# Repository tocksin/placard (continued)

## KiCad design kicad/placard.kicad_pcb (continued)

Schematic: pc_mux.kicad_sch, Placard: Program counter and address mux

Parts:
C3, C4, C7, C8, C9, C10: 100n; C_Disc_D5.0mm_W2.5mm_P5.00mm; MPN FG28X7R1H104KNT00
U3, U4, U7, U8, U9, U10: ATF22V10C-7PX; DIP-24_W7.62mm_Socket_Puller; MPN ATF22V10C-7PX

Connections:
+5V: C3.1, C4.1, C7.1, C8.1, C9.1, C10.1, U3.13 (CIN), U3.24 (VCC), U4.24 (VCC), U7.24 (VCC), U8.24 (VCC), U9.24 (VCC), U10.24 (VCC); also elsewhere on the board
ADDR0: U7.20 (LO0); also elsewhere on the board
ADDR1: U7.21 (LO1); also elsewhere on the board
ADDR2: U8.20 (LO0); also elsewhere on the board
ADDR3: U8.21 (LO1); also elsewhere on the board
ADDR4: U9.20 (LO0); also elsewhere on the board
ADDR5: U9.21 (LO1); also elsewhere on the board
ADDR6: U10.20 (LO0); also elsewhere on the board
ADDR7: U10.21 (LO1); also elsewhere on the board
ADDR8: U7.22 (HI0); also elsewhere on the board
ADDR9: U7.23 (HI1); also elsewhere on the board
ADDR10: U8.22 (HI0); also elsewhere on the board
ADDR11: U8.23 (HI1); also elsewhere on the board
ADDR12: U9.22 (HI0); also elsewhere on the board
ADDR13: U9.23 (HI1); also elsewhere on the board
ADDR14: U10.22 (HI0); also elsewhere on the board
ADDR15: U10.23 (HI1); also elsewhere on the board
CLK: U3.1 (CLK), U4.1 (CLK); also elsewhere on the board
D0: U7.5 (D0); also elsewhere on the board
D1: U7.9 (D1); also elsewhere on the board
D2: U8.5 (D0); also elsewhere on the board
D3: U8.9 (D1); also elsewhere on the board
D4: U9.5 (D0); also elsewhere on the board
D5: U9.9 (D1); also elsewhere on the board
D6: U10.5 (D0); also elsewhere on the board
D7: U10.9 (D1); also elsewhere on the board
DATABUS0: U3.2 (D0); also elsewhere on the board
DATABUS1: U3.3 (D1); also elsewhere on the board
DATABUS2: U3.4 (D2); also elsewhere on the board
DATABUS3: U3.5 (D3); also elsewhere on the board
DATABUS4: U3.6 (D4); also elsewhere on the board
DATABUS5: U3.7 (D5); also elsewhere on the board
DATABUS6: U3.8 (D6); also elsewhere on the board
DATABUS7: U3.9 (D7); also elsewhere on the board
GND: C3.2, C4.2, C7.2, C8.2, C9.2, C10.2, U3.12 (GND), U4.12 (GND), U7.12 (GND), U8.12 (GND), U9.12 (GND), U10.12 (GND); also elsewhere on the board
H3: U7.18 (V3); also elsewhere on the board
H4: U8.15 (V2); also elsewhere on the board
H5: U8.18 (V3); also elsewhere on the board
H6: U9.15 (V2); also elsewhere on the board
H7: U9.18 (V3); also elsewhere on the board
H8: U10.15 (V2); also elsewhere on the board
H9: U10.18 (V3); also elsewhere on the board
LOAD_PC_HIGH: U4.10 (LOAD); also elsewhere on the board
LOAD_PC_LOW: U3.10 (LOAD); also elsewhere on the board
unnamed: U3.23 (CO), U4.13 (CIN)
PC0: U3.15 (Q0), U7.8 (PC0)
PC1: U3.22 (Q1), U7.13 (PC1)
PC2: U3.21 (Q2), U8.8 (PC0)
PC3: U3.16 (Q3), U8.13 (PC1)
PC4: U3.20 (Q4), U9.8 (PC0)
PC5: U3.17 (Q5), U9.13 (PC1)
PC6: U3.19 (Q6), U10.8 (PC0)
PC7: U3.18 (Q7), U10.13 (PC1)
PC8: U4.15 (Q0), U7.16 (PC2)
PC9: U4.22 (Q1), U7.19 (PC3)
PC10: U4.21 (Q2), U8.16 (PC2)
PC11: U4.16 (Q3), U8.19 (PC3)
PC12: U4.20 (Q4), U9.16 (PC2)
PC13: U4.17 (Q5), U9.19 (PC3)
PC14: U4.19 (Q6), U10.16 (PC2)
PC15: U4.18 (Q7), U10.19 (PC3); also elsewhere on the board
PC_ENABLE: U3.11 (EN), U4.11 (EN), U7.2 (PC_ENABLE), U8.2 (PC_ENABLE), U9.2 (PC_ENABLE), U10.2 (PC_ENABLE); also elsewhere on the board
PIXEL_ENABLE: U7.1 (PIXEL_ENABLE), U8.1 (PIXEL_ENABLE), U9.1 (PIXEL_ENABLE), U10.1 (PIXEL_ENABLE); also elsewhere on the board
STALL_OUT: U3.14 (PIXEL_ENABLE), U4.14 (PIXEL_ENABLE); also elsewhere on the board
V2: U8.7 (V0); also elsewhere on the board
V3: U8.11 (V1); also elsewhere on the board
V4: U9.7 (V0); also elsewhere on the board
V5: U9.11 (V1); also elsewhere on the board
V6: U10.7 (V0); also elsewhere on the board
VA0: U7.7 (V0); also elsewhere on the board
VA1: U7.11 (V1); also elsewhere on the board
VA7: U10.11 (V1); also elsewhere on the board
VA8: U7.15 (V2); also elsewhere on the board
X0: U7.6 (X0); also elsewhere on the board
X1: U7.10 (X1); also elsewhere on the board
X2: U8.6 (X0); also elsewhere on the board
X3: U8.10 (X1); also elsewhere on the board
X4: U9.6 (X0); also elsewhere on the board
X5: U9.10 (X1); also elsewhere on the board
X6: U10.6 (X0); also elsewhere on the board
X7: U10.10 (X1); also elsewhere on the board
X_ENABLE: U7.3 (X_ENABLE), U8.3 (X_ENABLE), U9.3 (X_ENABLE), U10.3 (X_ENABLE); also elsewhere on the board
Y0: U4.2 (D0), U7.14 (Y2); also elsewhere on the board
Y1: U4.3 (D1), U7.17 (Y3); also elsewhere on the board
Y2: U4.4 (D2), U8.14 (Y2); also elsewhere on the board
Y3: U4.5 (D3), U8.17 (Y3); also elsewhere on the board
Y4: U4.6 (D4), U9.14 (Y2); also elsewhere on the board
Y5: U4.7 (D5), U9.17 (Y3); also elsewhere on the board
Y6: U4.8 (D6), U10.14 (Y2); also elsewhere on the board
Y7: U4.9 (D7), U10.17 (Y3); also elsewhere on the board
Y_ENABLE: U7.4 (Y_ENABLE), U8.4 (Y_ENABLE), U9.4 (Y_ENABLE), U10.4 (Y_ENABLE); also elsewhere on the board

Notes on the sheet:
Each mux: two low bits (D, X, video, PC) and two high bits (0, Y, video, PC); the enables select
Selects: PIXEL_ENABLE (U15) = video address; else PC_ENABLE = PC; else X_ENABLE / Y_ENABLE = X / Y register; else D / 00h.
Video address: VA0, VA1, VA7, VA8 from the audio slot PLD (line repeat), ADDR6:2 = V6:V2, ADDR15:9 = H9:H3.
Program counter and address mux
U3 CIN tied high (always counts); U3 CO carries into U4. STALL_OUT holds the PC (video reads, ALU wait, cartridge load).

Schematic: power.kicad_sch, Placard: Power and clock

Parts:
C40, C47: 1u; C_Disc_D5.0mm_W2.5mm_P5.00mm; MPN C330C105K5R5TA
C41: 220u; CP_Radial_D6.3mm_P2.50mm; MPN 25YXJ220M6.3X11
C43: 100n; C_Disc_D5.0mm_W2.5mm_P5.00mm; MPN FG28X7R1H104KNT00
D7: SA5.0A; D_DO-15_P10.16mm_Horizontal; MPN SA5.0A
D8: 1N5817; D_DO-41_SOD81_P7.62mm_Horizontal_Pad1.6; MPN 1N5817-TP
D18: WP7113ID; LED_D5.0mm; MPN WP7113ID
F1: 3 A hold; Fuse_Bourns_MF-RG300; MPN MF-RG300-0
J13: USB4125-GF-A; USB_C_Receptacle_GCT_USB4125_6P_HandSolder; MPN USB4125-GF-A-0190
JP1: STALL; PinHeader_1x02_P2.54mm_Vertical; MPN PREC002SAAN-RC
JP2: RUN; PinHeader_1x02_P2.54mm_Vertical; MPN PREC002SAAN-RC
K1: J1071CS5VDC.36; Relay_SPDT_CIT_J107; MPN J1071CS5VDC.36
NT1: AGND tie; NetTie-2_THT_Pad0.3mm
NT2: CLK tap; NetTie-2_THT_Pad0.3mm
R1, R2: 5.1k; R_Axial_DIN0207_L6.3mm_D2.5mm_P10.16mm_Horizontal_Value; MPN MFR-25FBF52-5K1
R3, R4: 10k; R_Axial_DIN0207_L6.3mm_D2.5mm_P10.16mm_Horizontal_Value; MPN MFR-25FBF52-10K
R59: 1k; R_Axial_DIN0207_L6.3mm_D2.5mm_P10.16mm_Horizontal_Value; MPN MFR-25FBF52-1K
R64: 22; R_Axial_DIN0207_L6.3mm_D2.5mm_P10.16mm_Horizontal_Value; MPN MFR-25FBF52-22R
SW1: ANT11TFHQE; SW_Toggle_CIT_ANT11TFHQE; MPN ANT11TFHQE
SW2: PTS645VL58-2 LFS; SW_Tactile_SPST_Angled_PTS645Vx58-2LFS; MPN PTS645VL58-2 LFS
TP1, TP2: GND; TestPoint_Keystone_5010-5014_Multipurpose; MPN 5011
TP3: +5V; TestPoint_Keystone_5010-5014_Multipurpose; MPN 5010
U40: MCP1700-3302E/TO; TO-92_Inline; MPN MCP1700-3302E/TO
X1: 25.175 MHz; Oscillator_DIP-14; MPN ECS-100A-251.7

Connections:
+3V3: C47.1, U40.3 (VO); also elsewhere on the board
+5V: C40.1, C41.1, C43.1, JP2.2 (B), K1.1, R3.1, R59.1, TP3.1, U40.2 (VI), X1.14 (VCC); also elsewhere on the board
/Power and clock/VON: K1.4, SW1.2 (B), SW2.1
CLK: NT2.2; also elsewhere on the board
CLK_E: NT2.1, X1.8 (OUT); also elsewhere on the board
GND: C40.2, C41.2, C43.2, C47.2, D7.2 (A), D8.2 (A), D18.1 (K), J13.A12 (GND), J13.B12 (GND), J13.S1 (SHIELD), K1.2, NT1.1, R1.2, R2.2, R4.2, R64.2, TP1.1, TP2.1, U40.1 (GND), X1.7 (GND); also elsewhere on the board
GNDA: NT1.2; also elsewhere on the board
unnamed: D7.1 (K), F1.2, SW1.1 (A)
unnamed: D8.1 (K), K1.5, SW2.2
unnamed: D18.2 (A), R59.2
unnamed: F1.1, J13.A9 (VBUS), J13.B9 (VBUS)
unnamed: J13.A5 (CC1), R1.1
unnamed: J13.B5 (CC2), R2.1
unnamed: K1.3, R64.1
RUN: JP2.1 (A), R4.1; also elsewhere on the board
STALL_IN: JP1.1 (A); also elsewhere on the board
STALL_OUT: JP1.2 (B), R3.2; also elsewhere on the board

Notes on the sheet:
here, at the power input
19 PLDs draw up to about 2.5 A (130 mA each at
-7, worst case): use a 3 A supply; the polyfuse
cartridge: STALL_IN (the Branch PLD's STALL) goes out to it.
5.1k on CC1 and CC2: a USB-C source gives 5 V.
AGND (audio) meets GND
USB-C 5 V in, 3.3 V for the SD card, 25.175 MHz oscillator (CLK), cartridge STALL and RUN
NT2: CLK_E (X1, U15 pin 9, U11 pin 1) to CLK (every other chip) through
D18 power LED (red, 5 mm) on +5V,
STALL_OUT (10k up) and RUN (10k down) come from the
one throw. SW2 reset: holding it pulls in K1,
TP1, TP2 GND (black Keystone 5011), TP3 +5V after K1
Power and clock
C40 input, C47 output (1 uF ceramic).
+5V via R64. C41 rides out the release bounce.
Without one, fit JP1 and JP2 for bring-up
R59 1k: about 3 mA.
whose NC contact opens the 5 V line; NO drains
after K1: dark while reset is held.
U40: 3.3 V for the SD card only (sheet 10).
(red 5010): clip points for the bring-up test leads.
at least 420 mm of track (500 nominal): the RAM /WE's early clock.
trips on a short. SW1 power: toggle, common +
(BRINGUP.md); take them out with a cartridge.

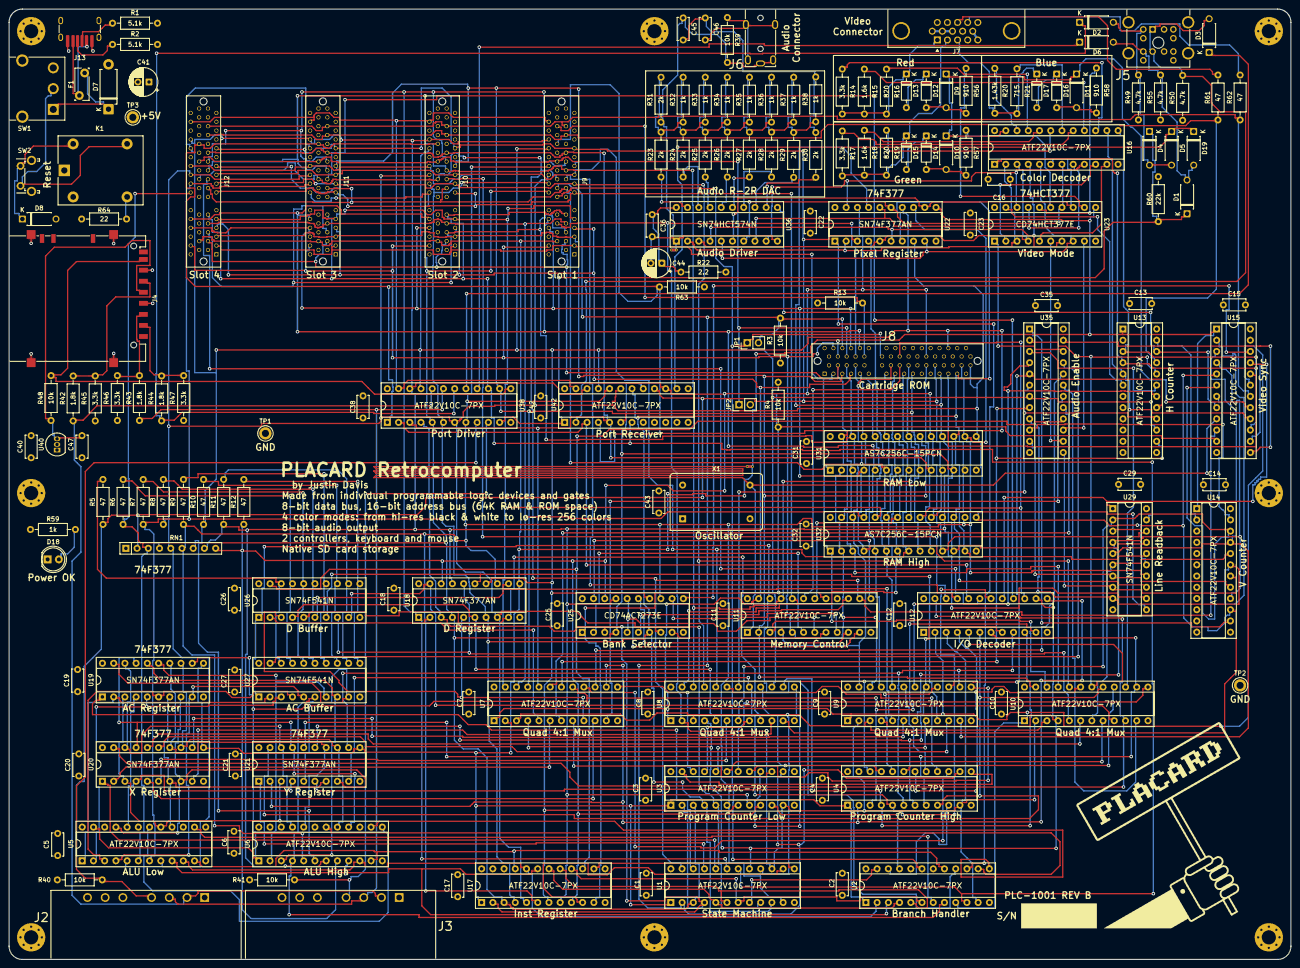
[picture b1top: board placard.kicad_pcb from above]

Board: 4 copper layers, 290.0 x 215.0 mm, 187 parts (0 on the bottom side), 255 nets.

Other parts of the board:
H1, H2, H3, H4, H5, H6, H7, H8: M3; MountingHole_3.2mm_M3_Pad_Via
LOGO1: PLACARD_Logo

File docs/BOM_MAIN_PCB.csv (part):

Qty,References,Part number,Manufacturer,Description,Value,Unit price USD,Line total USD,Price from,Notes,Footprint,On schematic
1,,PLC-1001 rev A,(custom PCB),"PCB, main board, 290 x 215 mm, 4-layer, 1.6 mm, HASL lead-free",,16.00,16.00,"est.: JLCPCB/PCBWay typical, KIT_PRICING.md",,,no
20,U1 U2 U3 U4 U5 U6 U7 U8 U9 U10 U11 U12 U13 U14 U15 U16 U17 U35 U38 U42,ATF22V10C-7PX,Microchip,"PLD, 22V10, 7.5 ns, PDIP-24 0.3"" (programmed)",,2.99,59.80,Mouser,"State U1; Branch U2; PC U3, U4; ALU U5, U6; Address mux U7-U10; Memory control U11; I/O decode U12; H counter U13; V counter U14; Sync U15; Color decoder U16; Instruction register U17; Audio slot U35; Shared port U38; PS/2 receiver U42",placard:DIP-24_W7.62mm_Socket_Puller,yes
5,U18 U19 U20 U21 U22,SN74F377AN,Texas Instruments,"Octal D flip-flop with enable, 74F, DIP-20",,1.54,7.70,Mouser,,placard:DIP-20_W7.62mm_Socket_Puller,yes
1,U23,CD74HCT377E,Texas Instruments,"Octal D flip-flop with enable, 74HCT, DIP-20 (line code: drives the row tint)",,1.29,1.29,Mouser,,placard:DIP-20_W7.62mm_Socket_Puller,yes
1,U25,CD74ACT273E,Texas Instruments,"Octal D flip-flop with clear, 74ACT, DIP-20",,2.45,2.45,Mouser,,placard:DIP-20_W7.62mm_Socket_Puller,yes
3,U26 U27 U29,SN74F541N,Texas Instruments,"Octal buffer, 3-state, 74F, DIP-20",,1.49,4.47,Mouser,,placard:DIP-20_W7.62mm_Socket_Puller,yes
2,U31 U32,AS7C256C-15PCN,Alliance Memory,"SRAM, 32K x 8, 15 ns, PDIP-28 0.3""",,15.21,30.42,Mouser,,placard:DIP-28_W7.62mm_Socket_Puller,yes
1,U36,SN74HCT574N,Texas Instruments,"Octal D flip-flop, 3-state, 74HCT, DIP-20",,1.46,1.46,Mouser,,placard:DIP-20_W7.62mm_Socket_Puller,yes
1,U40,MCP1700-3302E/TO,Microchip,"3.3 V LDO regulator, 250 mA, TO-92",,0.50,0.50,Mouser,,placard:TO-92_Inline,yes
1,X1,ECS-100A-251.7,ECS Inc.,"Clock oscillator, 25.175 MHz, 5 V, full-size DIP-14 can",25.175 MHz,4.06,4.06,"Digi-Key: Mouser has no stock (Justin, 2026-10-22)",,placard:Oscillator_DIP-14,yes
2,J2 J3,,,"SNES controller socket, 7 pin",SNES pad,4.00,8.00,est.: ZedLabz right-angle SNES port (Amazon/eBay),,placard:SNES_Pad_Socket_Horizontal,yes
1,J4,DM1AA-SF-PEJ(82),Hirose,SD card socket,SD (SPI),4.56,4.56,"Mouser: SMD, push-push (no horizontal through-hole SD socket exists; Kyocera 145638009511859+ went obsolete 2026-10-25)",,placard:SD_Hirose_DM1AA_SF_PEJ82,yes
1,J5,KMDGX-6S/6S-S4N,Kycon,"Stacked dual mini-DIN-6 receptacle (PS/2), right angle, shielded: mouse top, keyboard bottom",PS/2 kbd + mouse,3.72,3.72,Mouser,,placard:PS2_Kycon_KMDGX-6S-6S-S4N,yes
1,J6,54-00174,Tensility,"3.5 mm audio line out jack, 4 pole (TRRS), right angle, TH (a TRS plug's sleeve spans R2 and S)",3.5 mm,0.73,0.73,"Digi-Key: Justin, 2026-10-22",,placard:Jack_3.5mm_Tensility_54-00174_Horizontal,yes
1,J7,A-HDF 15 A-KG/T,Assmann WSW,"DE-15 high-density receptacle (VGA), with mounting holes",VGA,1.36,1.36,"Digi-Key: Justin, 2026-10-22",,placard:DSUB-15-HD_Female_Horizontal_P2.29x1.98mm_EdgePinOffset3.03mm_Housed_MountingHolesOffset4.94mm,yes
1,J8,87715-9106,Molex,"Cartridge slot: card edge, 64 contacts, 1.0 mm, keyed (PCIe x4 style), vertical TH",,2.88,2.88,Mouser,,placard:Molex_87715-9106_PCIe_x4_Vertical,yes
4,J9 J10 J11 J12,87715-9106,Molex,"Expansion slot: card edge, 64 contacts, 1.0 mm, keyed (PCIe x4 style), vertical TH, as the cartridge slot",,2.88,11.52,Mouser,"Optional (Justin, 2026-10-22): fit only the slots a card will go in; the computer runs with none.  The cartridge slot's connector since 2026-10-30 (EXPANSION.md)",placard:Molex_87715-9106_Expansion_Slot,yes
1,J13,USB4125-GF-A-0190,GCT,"USB-C receptacle, power only (6 pin), top mount",USB4125-GF-A,0.61,0.61,Mouser,,placard:USB_C_Receptacle_GCT_USB4125_6P_HandSolder,yes
1,SW1,ANT11TFHQE,CIT Relay and Switch,"Power on/off: SPDT on-on toggle, 5 A 28 V DC, right-angle PCB, 1/4-40 bushing",,4.50,4.50,est.: Digi-Key; Mouser has no stock,,placard:SW_Toggle_CIT_ANT11TFHQE,yes
1,SW2,PTS645VL58-2 LFS,C&K,"Reset button: tactile, SPST momentary, right angle, through hole (drives K1's coil)",,0.43,0.43,est.: Digi-Key; Mouser has no stock until 12/23/2026,,placard:SW_Tactile_SPST_Angled_PTS645Vx58-2LFS,yes
1,K1,J1071CS5VDC.36,CIT Relay and Switch,"Reset relay: SPDT, 5 V coil (69 ohm, 72 mA), 7 A 30 V DC (NO and NC), through hole, sealed; NC contact carries the 5 V",,1.15,1.15,"Digi-Key: Justin, 2026-10-25; Mouser does not sell CIT",,placard:Relay_SPDT_CIT_J107,yes
1,F1,MF-RG300-0,Bourns,"Polyfuse, 3 A hold, radial",3 A hold,0.73,0.73,Mouser,Part number from the footprint (Fuse_Bourns_MF-RG300),placard:Fuse_Bourns_MF-RG300,yes
11,D1 D2 D3 D4 D5 D6 D8 D9 D10 D11 D19,1N5817-TP,Micro Commercial Co,"Schottky diode, 1 A, DO-41 (black)",1N5817,0.15,1.65,est.: MCC 1N5817-TP,"Black DO-41 Schottky, so it is not mixed up with the glass 1N4148s; any 1N5817 (MCC, onsemi, Diodes Inc.)",placard:D_DO-41_SOD81_P7.62mm_Horizontal_Pad1.6,yes
1,D7,SA5.0A,Littelfuse,"TVS diode, 5 V stand-off, 500 W, DO-15 axial (across the fused USB 5 V)",,0.64,0.64,Mouser,,placard:D_DO-15_P10.16mm_Horizontal,yes
6,D12 D13 D14 D15 D16 D17,1N4148-TAP,Vishay,"Small-signal diode, DO-35 (glass)",1N4148,0.26,1.56,Mouser: Vishay 1N4148-TAP,"Any 1N4148 (Vishay, onsemi, Diodes Inc.)",placard:D_DO-35_SOD27_P7.62mm_Horizontal,yes
1,D18,WP7113ID,Kingbright,"Power LED, 5 mm, red diffused, through hole (on +5V after K1)",,0.21,0.21,Mouser,"D18 with R59 (1k, about 3 mA); any 5 mm LED fits, pick the color (was Lite-On LTL2R3KRD-EM, out of stock 2026-10-25)",placard:LED_D5.0mm,yes
2,R1 R2,MFR-25FBF52-5K1,Yageo,"Resistor, metal film 1%, 1/4 W, axial",5.1k,0.10,0.20,est.: Yageo MFR-25FBF52 series,,placard:R_Axial_DIN0207_L6.3mm_D2.5mm_P10.16mm_Horizontal_Value,yes
8,R3 R4 R13 R39 R40 R41 R48 R63,MFR-25FBF52-10K,Yageo,"Resistor, metal film 1%, 1/4 W, axial",10k,0.10,0.80,est.: Yageo MFR-25FBF52 series,,placard:R_Axial_DIN0207_L6.3mm_D2.5mm_P10.16mm_Horizontal_Value,yes
10,R5 R6 R7 R8 R9 R10 R11 R12 R61 R62,MFR-25FBF52-47R,Yageo,"Resistor, metal film 1%, 1/4 W, axial",47,0.04,0.40,est.: Yageo MFR-25FBF52 series,,placard:R_Axial_DIN0207_L6.3mm_D2.5mm_P10.16mm_Horizontal_Value,yes
5,R14 R17 R45 R46 R47,MFR-25FBF52-3K3,Yageo,"Resistor, metal film 1%, 1/4 W, axial",3.3k,0.10,0.50,est.: Yageo MFR-25FBF52 series,,placard:R_Axial_DIN0207_L6.3mm_D2.5mm_P10.16mm_Horizontal_Value,yes
2,R15 R18,MFR-25FBF52-1K6,Yageo,"Resistor, metal film 1%, 1/4 W, axial",1.6k,0.10,0.20,est.: Yageo MFR-25FBF52 series,,placard:R_Axial_DIN0207_L6.3mm_D2.5mm_P10.16mm_Horizontal_Value,yes
2,R16 R19,MFR-25FBF52-820R,Yageo,"Resistor, metal film 1%, 1/4 W, axial",820,0.10,0.20,est.: Yageo MFR-25FBF52 series,,placard:R_Axial_DIN0207_L6.3mm_D2.5mm_P10.16mm_Horizontal_Value,yes
1,R20,MFR-25FBF52-1K43,Yageo,"Resistor, metal film 1%, 1/4 W, axial",1.43k,0.10,0.10,est.: Yageo MFR-25FBF52 series,,placard:R_Axial_DIN0207_L6.3mm_D2.5mm_P10.16mm_Horizontal_Value,yes
1,R21,MFR-25FBF52-715R,Yageo,"Resistor, metal film 1%, 1/4 W, axial",715,0.10,0.10,est.: Yageo MFR-25FBF52 series,,placard:R_Axial_DIN0207_L6.3mm_D2.5mm_P10.16mm_Horizontal_Value,yes
1,R22,MFR-25FBF52-2R2,Yageo,"Resistor, metal film 1%, 1/4 W, axial",2.2,0.10,0.10,est.: Yageo MFR-25FBF52 series,,placard:R_Axial_DIN0207_L6.3mm_D2.5mm_P10.16mm_Horizontal_Value,yes
9,R23 R24 R25 R26 R27 R28 R29 R30 R31,MFR-25FBF52-2K,Yageo,"Resistor, metal film 1%, 1/4 W, axial",2k,0.10,0.90,est.: Yageo MFR-25FBF52 series,,placard:R_Axial_DIN0207_L6.3mm_D2.5mm_P10.16mm_Horizontal_Value,yes
12,R32 R33 R34 R35 R36 R37 R38 R51 R52 R53 R54 R59,MFR-25FBF52-1K,Yageo,"Resistor, metal film 1%, 1/4 W, axial",1k,0.04,0.48,est.: Yageo MFR-25FBF52 series,,placard:R_Axial_DIN0207_L6.3mm_D2.5mm_P10.16mm_Horizontal_Value,yes
3,R42 R43 R44,MFR-25FBF52-1K8,Yageo,"Resistor, metal film 1%, 1/4 W, axial",1.8k,0.10,0.30,est.: Yageo MFR-25FBF52 series,,placard:R_Axial_DIN0207_L6.3mm_D2.5mm_P10.16mm_Horizontal_Value,yes
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
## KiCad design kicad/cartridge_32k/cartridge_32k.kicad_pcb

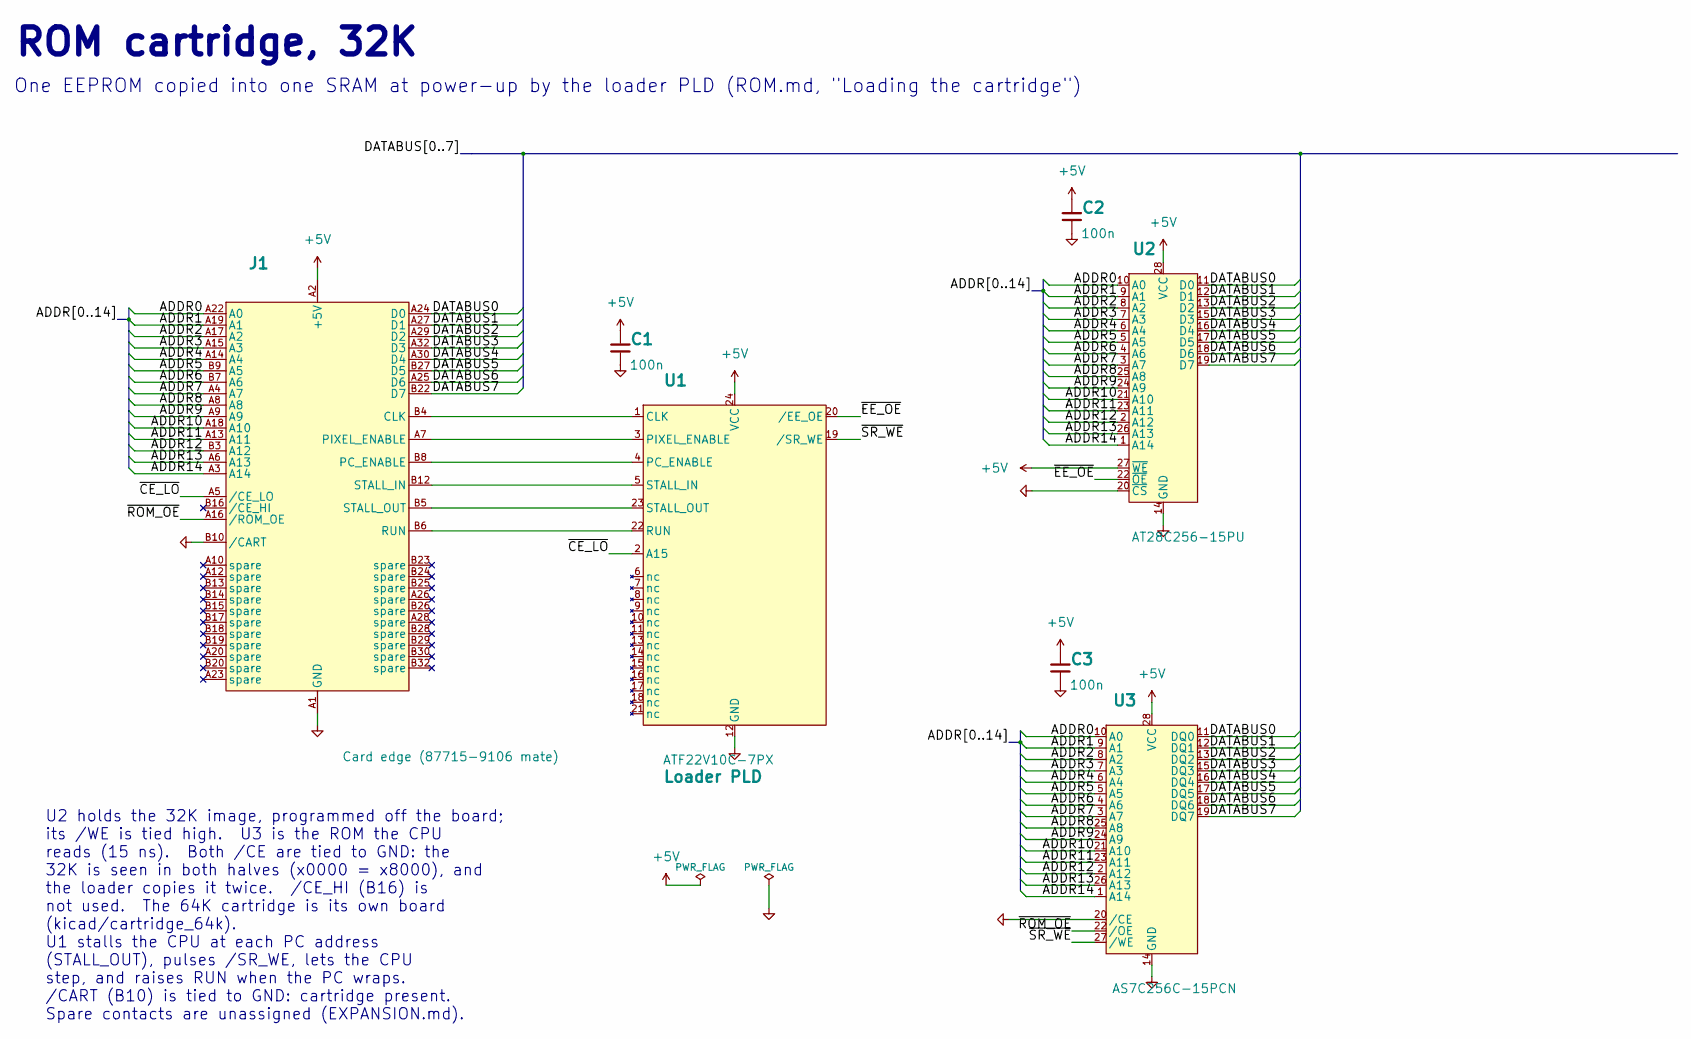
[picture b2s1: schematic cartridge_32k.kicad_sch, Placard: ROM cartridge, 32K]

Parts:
C1, C2, C3: 100n; C_Disc_D5.0mm_W2.5mm_P5.00mm; MPN FG28X7R1H104KNT00
J1: Card edge (87715-9106 mate); Card_Edge_87715-9106
U1: ATF22V10C-7PX; DIP-24_W7.62mm_Socket_Puller; MPN ATF22V10C-7PX
U2: AT28C256-15PU; DIP-28_W15.24mm_Socket_Puller; MPN AT28C256-15PU
U3: AS7C256C-15PCN; DIP-28_W7.62mm_Socket_Puller; MPN AS7C256C-15PCN

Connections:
+5V: C1.1, C2.1, C3.1, J1.A2 (+5V), J1.B2 (+5V), U1.24 (VCC), U2.27 (~WE), U2.28 (VCC), U3.28 (VCC)
/ADDR0: J1.A22 (A0), U2.10 (A0), U3.10 (A0)
/ADDR1: J1.A19 (A1), U2.9 (A1), U3.9 (A1)
/ADDR2: J1.A17 (A2), U2.8 (A2), U3.8 (A2)
/ADDR3: J1.A15 (A3), U2.7 (A3), U3.7 (A3)
/ADDR4: J1.A14 (A4), U2.6 (A4), U3.6 (A4)
/ADDR5: J1.B9 (A5), U2.5 (A5), U3.5 (A5)
/ADDR6: J1.B7 (A6), U2.4 (A6), U3.4 (A6)
/ADDR7: J1.A4 (A7), U2.3 (A7), U3.3 (A7)
/ADDR8: J1.A8, U2.25 (A8), U3.25 (A8)
/ADDR9: J1.A9, U2.24 (A9), U3.24 (A9)
/ADDR10: J1.A18 (A10), U2.21 (A10), U3.21 (A10)
/ADDR11: J1.A13 (A11), U2.23 (A11), U3.23 (A11)
/ADDR12: J1.B3 (A12), U2.2 (A12), U3.2 (A12)
/ADDR13: J1.A6 (A13), U2.26 (A13), U3.26 (A13)
/ADDR14: J1.A3 (A14), U2.1 (A14), U3.1 (A14)
/DATABUS0: J1.A24 (D0), U2.11 (D0), U3.11 (DQ0)
/DATABUS1: J1.A27 (D1), U2.12 (D1), U3.12 (DQ1)
/DATABUS2: J1.A29 (D2), U2.13 (D2), U3.13 (DQ2)
/DATABUS3: J1.A32 (D3), U2.15 (D3), U3.15 (DQ3)
/DATABUS4: J1.A30 (D4), U2.16 (D4), U3.16 (DQ4)
/DATABUS5: J1.B27 (D5), U2.17 (D5), U3.17 (DQ5)
/DATABUS6: J1.A25 (D6), U2.18 (D6), U3.18 (DQ6)
/DATABUS7: J1.B22 (D7), U2.19 (D7), U3.19 (DQ7)
/~CE_LO: J1.A5 (/CE_LO), U1.2 (A15)
/~EE_OE: U1.20 (/EE_OE), U2.22 (~OE)
/~ROM_OE: J1.A16 (/ROM_OE), U3.22 (/OE)
/~SR_WE: U1.19 (/SR_WE), U3.27 (/WE)
GND: C1.2, C2.2, C3.2, J1.A1 (GND), J1.A11 (GND), J1.A21 (GND), J1.A31 (GND), J1.B1 (GND), J1.B10 (/CART), J1.B11 (GND), J1.B21 (GND), J1.B31 (GND), U1.12 (GND), U2.14 (GND), U2.20 (~CS), U3.14 (GND), U3.20 (/CE)
unnamed: J1.B4 (CLK), U1.1 (CLK)
unnamed: J1.B8 (PC_ENABLE), U1.4 (PC_ENABLE)
unnamed: J1.A7 (PIXEL_ENABLE), U1.3 (PIXEL_ENABLE)
unnamed: J1.B6 (RUN), U1.22 (RUN)
unnamed: J1.B12 (STALL_IN), U1.5 (STALL_IN)
unnamed: J1.B5 (STALL_OUT), U1.23 (STALL_OUT)

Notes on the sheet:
ROM cartridge, 32K
One EEPROM copied into one SRAM at power-up by the loader PLD (ROM.md, "Loading the cartridge")
U2 holds the 32K image, programmed off the board;
its /WE is tied high. U3 is the ROM the CPU
reads (15 ns). Both /CE are tied to GND: the
32K is seen in both halves (x0000 = x8000), and
the loader copies it twice. /CE_HI (B16) is
not used. The 64K cartridge is its own board
(kicad/cartridge_64k).
U1 stalls the CPU at each PC address
(STALL_OUT), pulses /SR_WE, lets the CPU
step, and raises RUN when the PC wraps.
/CART (B10) is tied to GND: cartridge present.
Spare contacts are unassigned (EXPANSION.md).

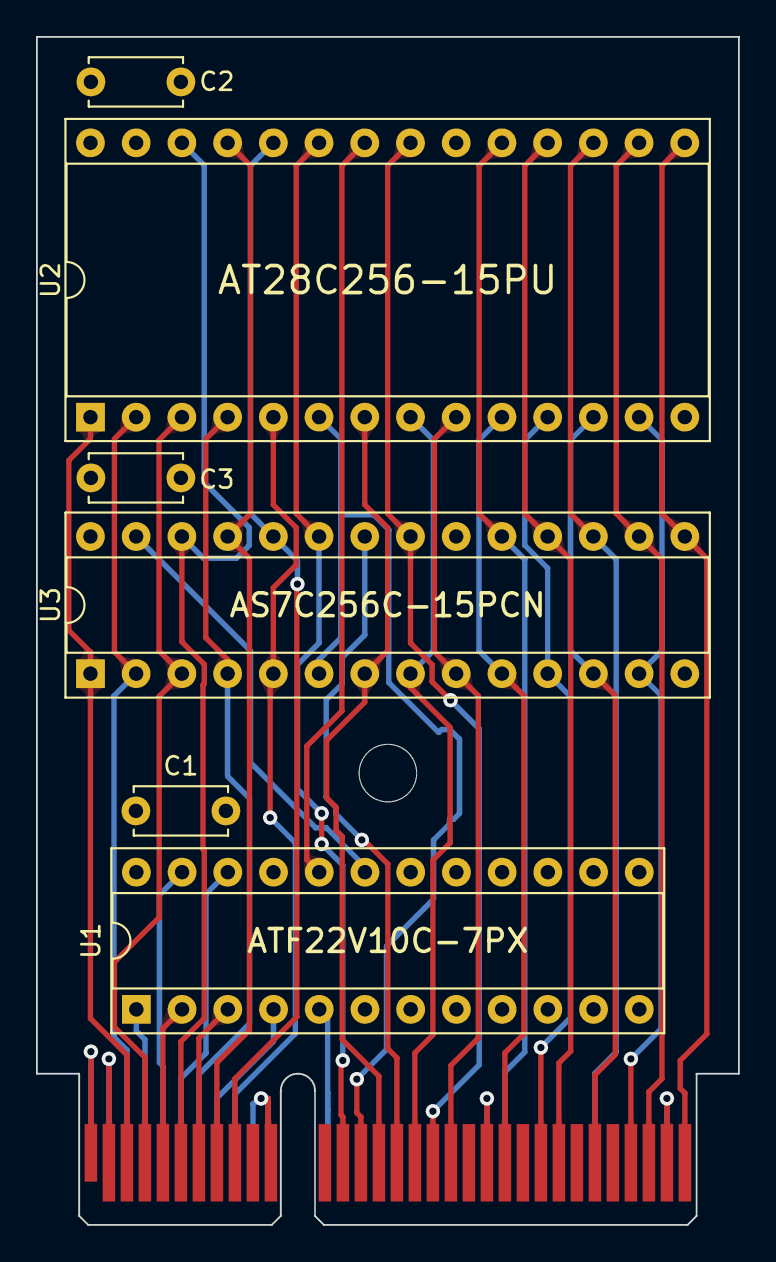
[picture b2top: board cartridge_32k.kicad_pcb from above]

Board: 4 copper layers, 39.0 x 66.0 mm, 8 parts (0 on the bottom side), 35 nets.

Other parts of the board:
H1: M3; MountingHole_3.2mm_M3

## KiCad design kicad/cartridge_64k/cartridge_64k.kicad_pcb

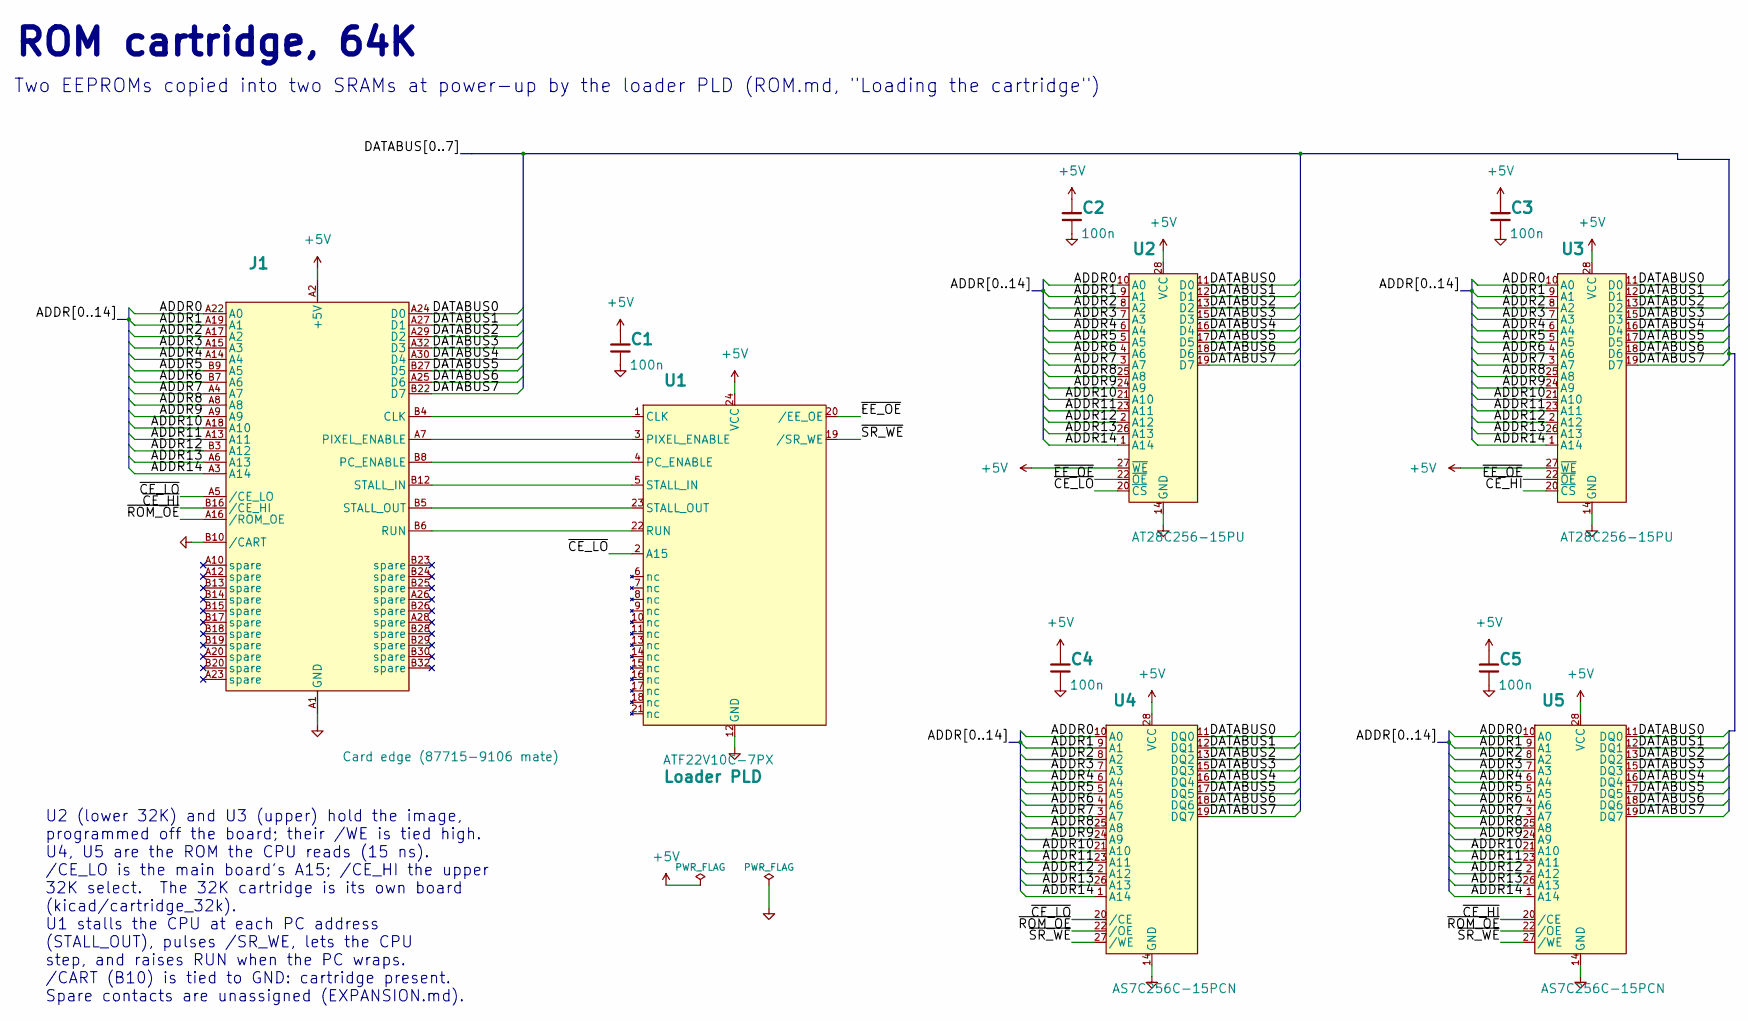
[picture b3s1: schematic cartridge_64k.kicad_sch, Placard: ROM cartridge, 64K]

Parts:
C1, C2, C3, C4, C5: 100n; C_Disc_D5.0mm_W2.5mm_P5.00mm; MPN FG28X7R1H104KNT00
J1: Card edge (87715-9106 mate); Card_Edge_87715-9106
U1: ATF22V10C-7PX; DIP-24_W7.62mm_Socket_Puller; MPN ATF22V10C-7PX
U2, U3: AT28C256-15PU; DIP-28_W15.24mm_Socket_Puller; MPN AT28C256-15PU
U4, U5: AS7C256C-15PCN; DIP-28_W7.62mm_Socket_Puller; MPN AS7C256C-15PCN

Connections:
+5V: C1.1, C2.1, C3.1, C4.1, C5.1, J1.A2 (+5V), J1.B2 (+5V), U1.24 (VCC), U2.27 (~WE), U2.28 (VCC), U3.27 (~WE), U3.28 (VCC), U4.28 (VCC), U5.28 (VCC)
/ADDR0: J1.A22 (A0), U2.10 (A0), U3.10 (A0), U4.10 (A0), U5.10 (A0)
/ADDR1: J1.A19 (A1), U2.9 (A1), U3.9 (A1), U4.9 (A1), U5.9 (A1)
/ADDR2: J1.A17 (A2), U2.8 (A2), U3.8 (A2), U4.8 (A2), U5.8 (A2)
/ADDR3: J1.A15 (A3), U2.7 (A3), U3.7 (A3), U4.7 (A3), U5.7 (A3)
/ADDR4: J1.A14 (A4), U2.6 (A4), U3.6 (A4), U4.6 (A4), U5.6 (A4)
/ADDR5: J1.B9 (A5), U2.5 (A5), U3.5 (A5), U4.5 (A5), U5.5 (A5)
/ADDR6: J1.B7 (A6), U2.4 (A6), U3.4 (A6), U4.4 (A6), U5.4 (A6)
/ADDR7: J1.A4 (A7), U2.3 (A7), U3.3 (A7), U4.3 (A7), U5.3 (A7)
/ADDR8: J1.A8, U2.25 (A8), U3.25 (A8), U4.25 (A8), U5.25 (A8)
/ADDR9: J1.A9, U2.24 (A9), U3.24 (A9), U4.24 (A9), U5.24 (A9)
/ADDR10: J1.A18 (A10), U2.21 (A10), U3.21 (A10), U4.21 (A10), U5.21 (A10)
/ADDR11: J1.A13 (A11), U2.23 (A11), U3.23 (A11), U4.23 (A11), U5.23 (A11)
/ADDR12: J1.B3 (A12), U2.2 (A12), U3.2 (A12), U4.2 (A12), U5.2 (A12)
/ADDR13: J1.A6 (A13), U2.26 (A13), U3.26 (A13), U4.26 (A13), U5.26 (A13)
/ADDR14: J1.A3 (A14), U2.1 (A14), U3.1 (A14), U4.1 (A14), U5.1 (A14)
/DATABUS0: J1.A24 (D0), U2.11 (D0), U3.11 (D0), U4.11 (DQ0), U5.11 (DQ0)
/DATABUS1: J1.A27 (D1), U2.12 (D1), U3.12 (D1), U4.12 (DQ1), U5.12 (DQ1)
/DATABUS2: J1.A29 (D2), U2.13 (D2), U3.13 (D2), U4.13 (DQ2), U5.13 (DQ2)
/DATABUS3: J1.A32 (D3), U2.15 (D3), U3.15 (D3), U4.15 (DQ3), U5.15 (DQ3)
/DATABUS4: J1.A30 (D4), U2.16 (D4), U3.16 (D4), U4.16 (DQ4), U5.16 (DQ4)
/DATABUS5: J1.B27 (D5), U2.17 (D5), U3.17 (D5), U4.17 (DQ5), U5.17 (DQ5)
/DATABUS6: J1.A25 (D6), U2.18 (D6), U3.18 (D6), U4.18 (DQ6), U5.18 (DQ6)
/DATABUS7: J1.B22 (D7), U2.19 (D7), U3.19 (D7), U4.19 (DQ7), U5.19 (DQ7)
/~CE_HI: J1.B16 (/CE_HI), U3.20 (~CS), U5.20 (/CE)
/~CE_LO: J1.A5 (/CE_LO), U1.2 (A15), U2.20 (~CS), U4.20 (/CE)
/~EE_OE: U1.20 (/EE_OE), U2.22 (~OE), U3.22 (~OE)
/~ROM_OE: J1.A16 (/ROM_OE), U4.22 (/OE), U5.22 (/OE)
/~SR_WE: U1.19 (/SR_WE), U4.27 (/WE), U5.27 (/WE)
GND: C1.2, C2.2, C3.2, C4.2, C5.2, J1.A1 (GND), J1.A11 (GND), J1.A21 (GND), J1.A31 (GND), J1.B1 (GND), J1.B10 (/CART), J1.B11 (GND), J1.B21 (GND), J1.B31 (GND), U1.12 (GND), U2.14 (GND), U3.14 (GND), U4.14 (GND), U5.14 (GND)
unnamed: J1.B4 (CLK), U1.1 (CLK)
unnamed: J1.B8 (PC_ENABLE), U1.4 (PC_ENABLE)
unnamed: J1.A7 (PIXEL_ENABLE), U1.3 (PIXEL_ENABLE)
unnamed: J1.B6 (RUN), U1.22 (RUN)
unnamed: J1.B12 (STALL_IN), U1.5 (STALL_IN)
unnamed: J1.B5 (STALL_OUT), U1.23 (STALL_OUT)

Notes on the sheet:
ROM cartridge, 64K
Two EEPROMs copied into two SRAMs at power-up by the loader PLD (ROM.md, "Loading the cartridge")
U2 (lower 32K) and U3 (upper) hold the image,
programmed off the board; their /WE is tied high.
U4, U5 are the ROM the CPU reads (15 ns).
/CE_LO is the main board's A15; /CE_HI the upper
32K select. The 32K cartridge is its own board
(kicad/cartridge_32k).
U1 stalls the CPU at each PC address
(STALL_OUT), pulses /SR_WE, lets the CPU
step, and raises RUN when the PC wraps.
/CART (B10) is tied to GND: cartridge present.
Spare contacts are unassigned (EXPANSION.md).

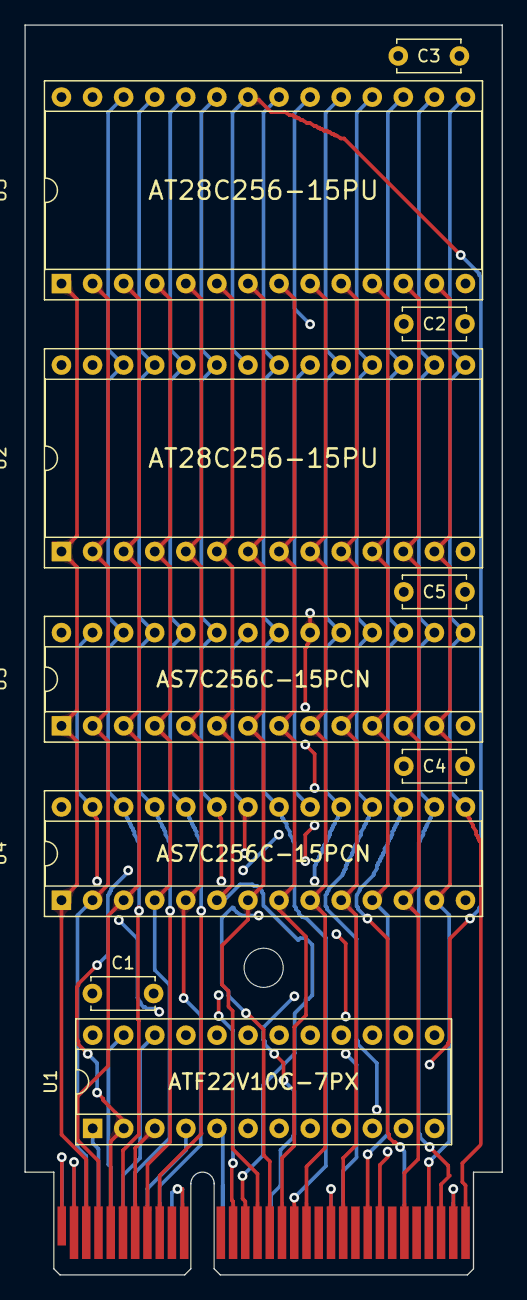
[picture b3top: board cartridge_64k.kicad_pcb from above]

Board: 4 copper layers, 39.0 x 102.2 mm, 12 parts (0 on the bottom side), 36 nets.

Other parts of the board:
H1: M3; MountingHole_3.2mm_M3
